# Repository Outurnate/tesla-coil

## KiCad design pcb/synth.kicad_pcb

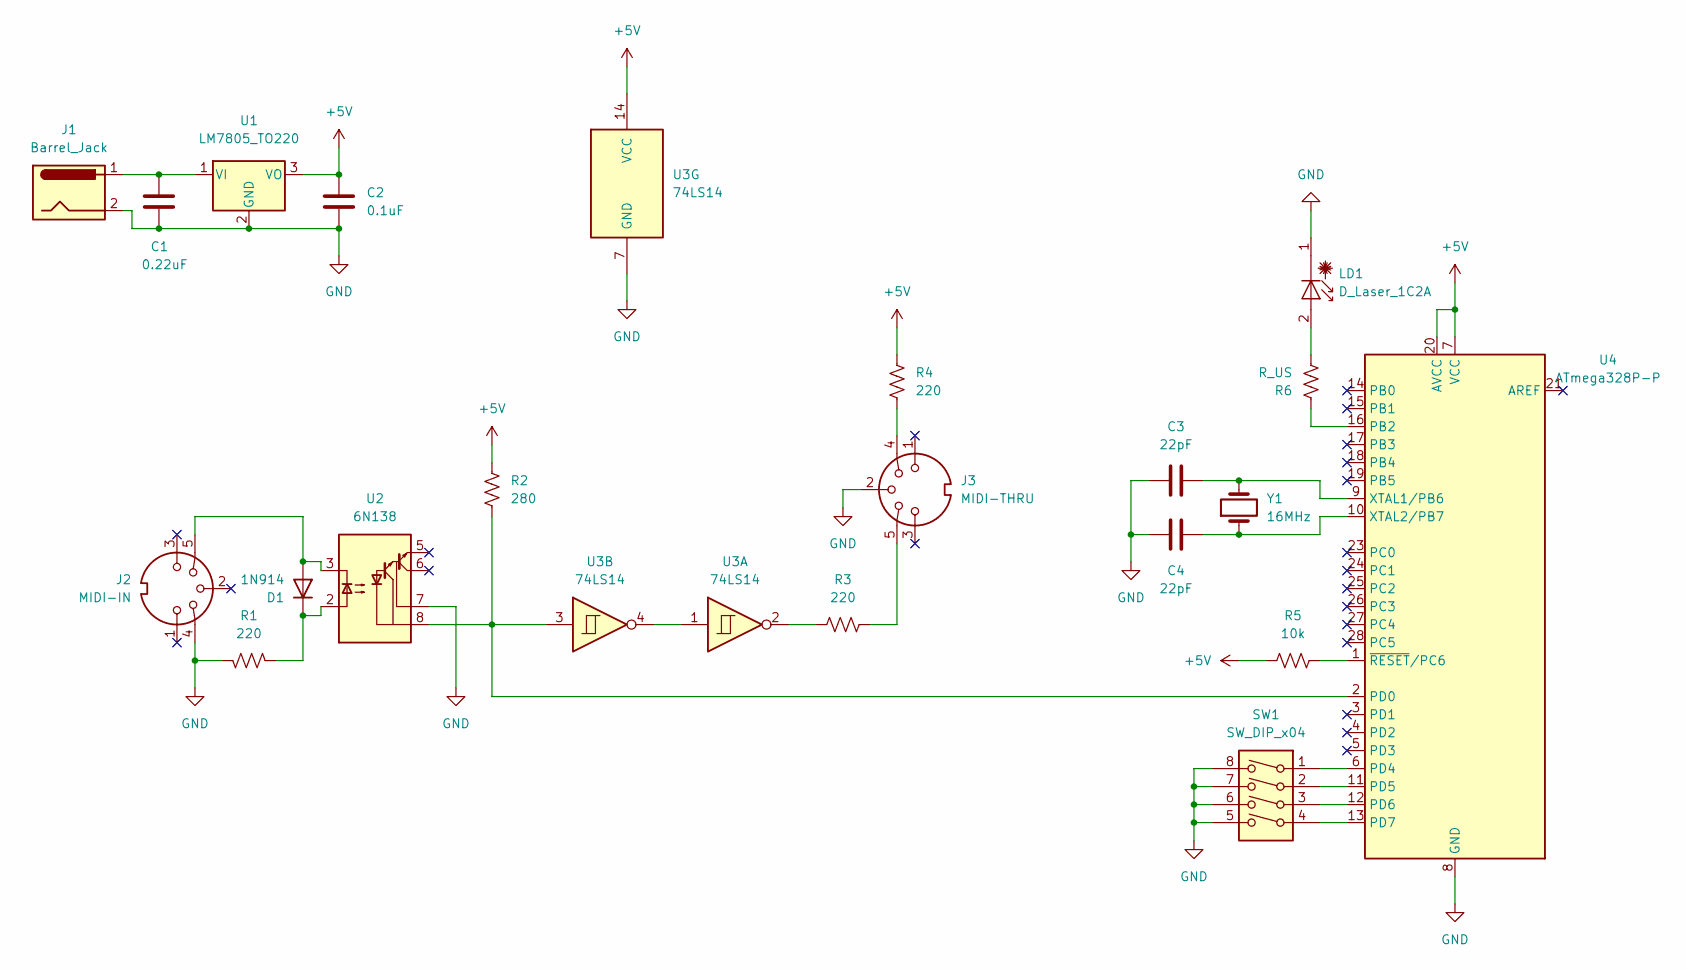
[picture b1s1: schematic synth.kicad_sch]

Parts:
C1: 0.22uF; C_Disc_D5.0mm_W2.5mm_P2.50mm
C2: 0.1uF; C_Disc_D5.0mm_W2.5mm_P2.50mm
C3, C4: 22pF; C_Disc_D5.0mm_W2.5mm_P2.50mm
D1: 1N914; D_DO-35_SOD27_P7.62mm_Horizontal
J1: Barrel_Jack; CUI_PJ-037A
J2: MIDI-IN; CUI_SDS-50J
J3: MIDI-THRU; CUI_SDS-50J
LD1: D_Laser_1C2A; PinHeader_1x02_P2.54mm_Vertical
R1, R3, R4: 220; R_Axial_DIN0207_L6.3mm_D2.5mm_P10.16mm_Horizontal
R2: 280; R_Axial_DIN0207_L6.3mm_D2.5mm_P10.16mm_Horizontal
R5: 10k; R_Axial_DIN0207_L6.3mm_D2.5mm_P10.16mm_Horizontal
R6: R_US; R_Axial_DIN0207_L6.3mm_D2.5mm_P10.16mm_Horizontal
SW1: SW_DIP_x04; SW_DIP_SPSTx04_Slide_9.78x12.34mm_W7.62mm_P2.54mm
U1: LM7805_TO220; TO-220-3_Vertical
U2: 6N138; DIP-8_W7.62mm_Socket
U3: 74LS14; DIP-14_W7.62mm_Socket
U4: ATmega328P-P; DIP-28_W7.62mm_Socket
Y1: 16MHz; Crystal_HC49-U_Vertical

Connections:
+5V: C2.1, R2.1, R4.1, R5.2, U1.3 (VO), U3.14 (VCC), U4.7 (VCC), U4.20 (AVCC)
GND: C1.2, C2.2, C3.2, C4.1, J1.2, J2.4, J3.2, LD1.1 (K), R1.2, SW1.5, SW1.6, SW1.7, SW1.8, U1.2 (GND), U2.7 (VO1), U3.7 (GND), U4.8 (GND), U4.22 (GND)
unnamed: C1.1, J1.1, U1.1 (VI)
unnamed: C3.1, U4.9 (XTAL1/PB6), Y1.2
unnamed: C4.2, U4.10 (XTAL2/PB7), Y1.1
unnamed: D1.1 (K), R1.1, U2.2 (C1)
unnamed: D1.2 (A), J2.5, U2.3 (C2)
unnamed: J3.4, R4.2
unnamed: J3.5, R3.1
unnamed: LD1.2 (A), R6.2
unnamed: R2.2, U2.8 (VCC), U3.3, U4.2 (PD0)
unnamed: R3.2, U3.2
unnamed: R5.1, U4.1 (~RESET/PC6)
unnamed: R6.1, U4.16 (PB2)
unnamed: SW1.1, U4.6 (PD4)
unnamed: SW1.2, U4.11 (PD5)
unnamed: SW1.3, U4.12 (PD6)
unnamed: SW1.4, U4.13 (PD7)
unnamed: U3.1, U3.4

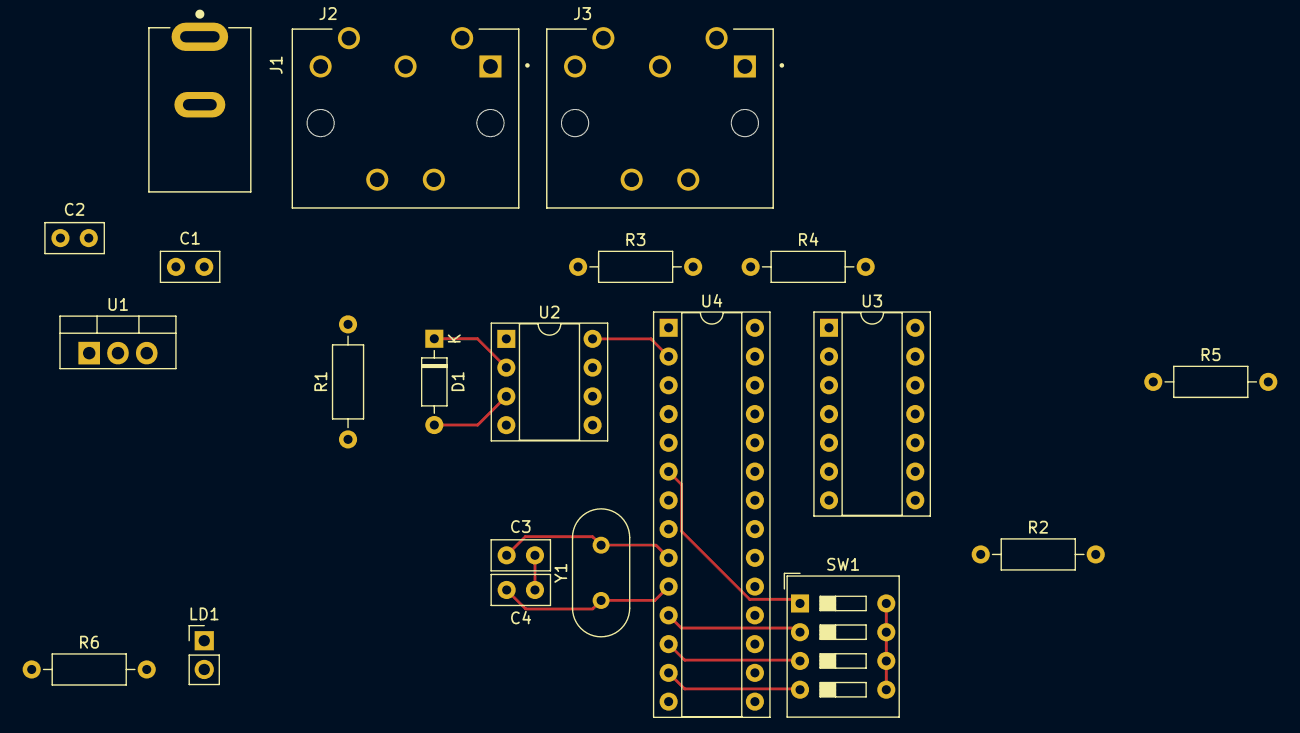
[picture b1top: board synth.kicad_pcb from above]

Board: 2 copper layers, 21 parts (0 on the bottom side), 19 nets.

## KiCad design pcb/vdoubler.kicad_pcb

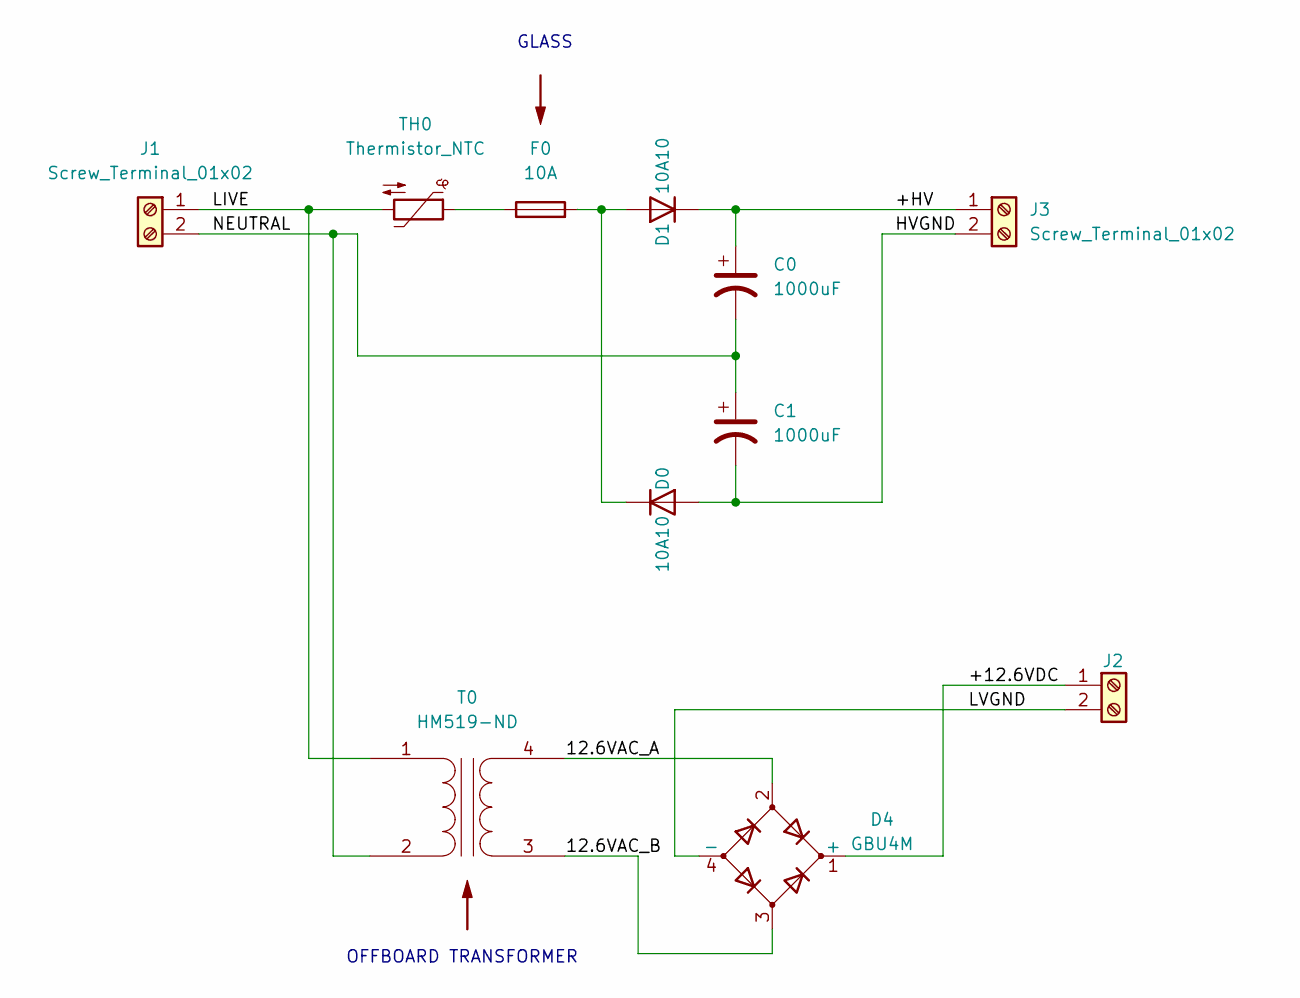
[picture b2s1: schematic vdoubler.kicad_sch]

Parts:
C0, C1: 1000uF; CP_Radial_D30.0mm_P10.00mm_SnapIn; DigiKey Part Number 399-ELH108M250AS5AA-ND
D0, D1: 10A10; D_P600_R-6_P12.70mm_Horizontal; DigiKey Part Number 3191-10A10-C1-3000-ND
D4: GBU4M; Diode_Bridge_Vishay_GBU; DigiKey Part Number GBU4M-ND
F0: 10A; Fuseholder_Cylinder-5x20mm_Bulgin_FX0456_Vertical_Closed; DigiKey Part Number 708-1427-ND
J1, J2, J3: Screw_Terminal_01x02; TE_1546833-2; DigiKey Part Number A112378-ND
T0: HM519-ND; TE_1546833-4; DigiKey Part Number HM519-ND
TH0: Thermistor_NTC; RV_Disc_D21.5mm_W4.3mm_P10mm; DigiKey Part Number 570-1354-ND

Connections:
/12.6VAC_A: D4.2, T0.4 (SB)
/12.6VAC_B: D4.3, T0.3 (SA)
/+12.6VDC: D4.1 (+), J2.1
/+HV: C0.1, D1.1 (K), J3.1
/HVGND: C1.2, D0.2 (A), J3.2
/LIVE: J1.1, T0.1 (AA), TH0.2
/LVGND: D4.4 (-), J2.2
/NEUTRAL: C0.2, C1.1, J1.2, T0.2 (AB)
unnamed: D0.1 (K), D1.2 (A), F0.2
unnamed: F0.1, TH0.1

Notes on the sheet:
GLASS
OFFBOARD TRANSFORMER

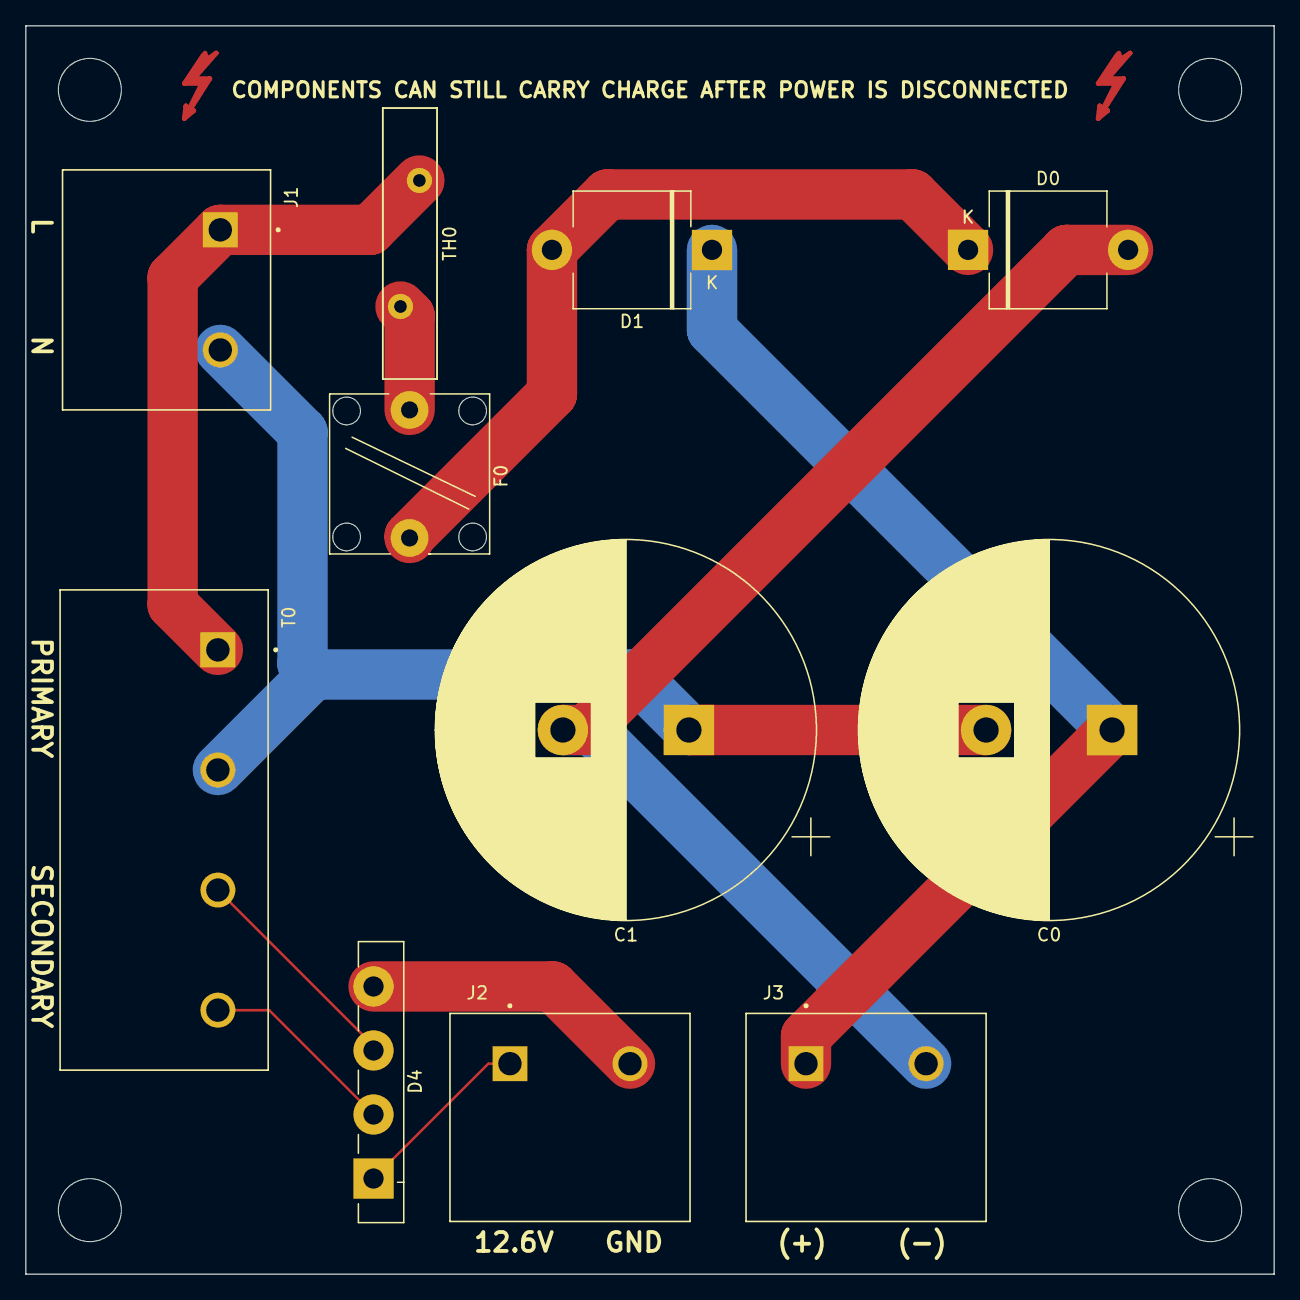
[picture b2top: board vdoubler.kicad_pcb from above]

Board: 2 copper layers, 99.1 x 99.1 mm, 11 parts (0 on the bottom side), 10 nets.

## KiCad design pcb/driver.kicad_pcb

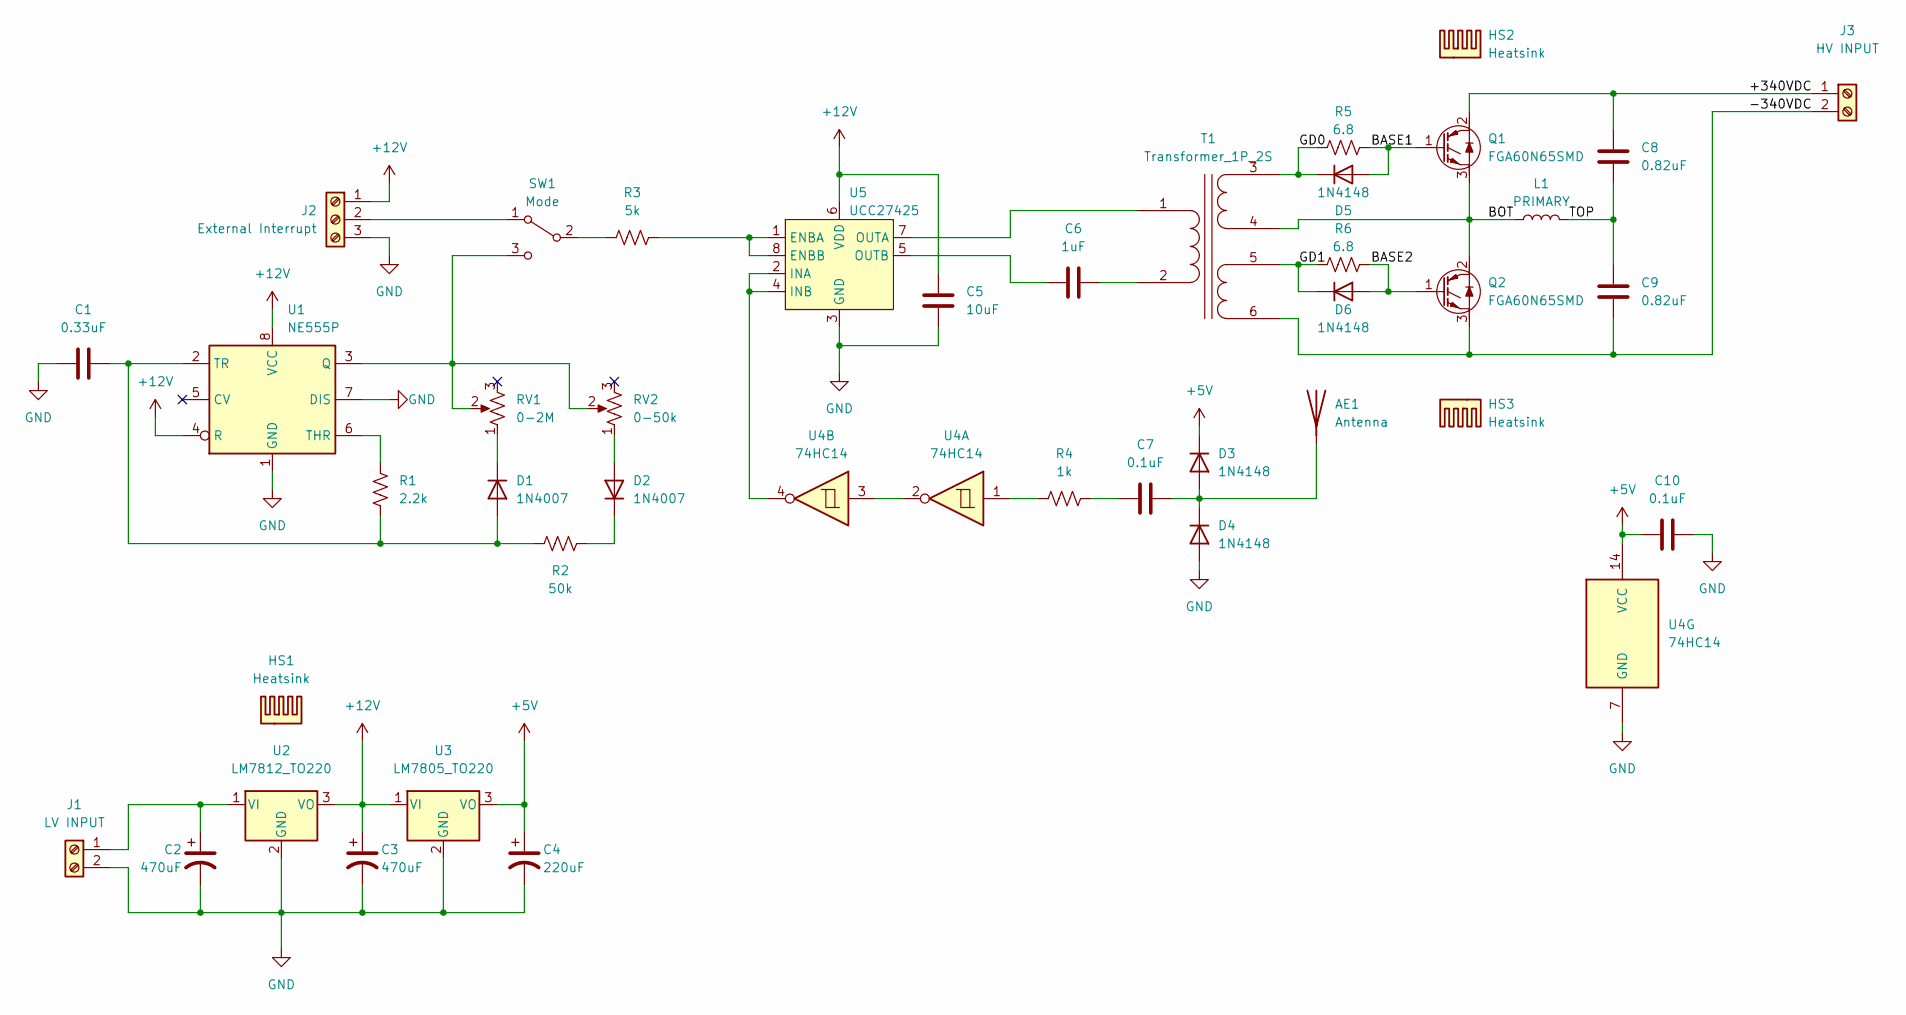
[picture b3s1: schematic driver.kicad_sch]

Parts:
AE1: Antenna; PinHeader_1x01_P2.54mm_Vertical
C1: 0.33uF; C_Rect_L7.0mm_W3.5mm_P5.00mm; DigiKey Part Number 445-180638-1-ND
C2, C3: 470uF; CP_Radial_D10.0mm_P5.00mm; DigiKey Part Number 1189-1869-ND
C4: 220uF; CP_Radial_D8.0mm_P3.50mm; DigiKey Part Number 732-8829-1-ND
C5: 10uF; C_Rect_L7.0mm_W3.5mm_P5.00mm; DigiKey Part Number 445-FG26X7R1E106KRT00-ND
C6: 1uF; C_Rect_L7.0mm_W3.5mm_P5.00mm; DigiKey Part Number 445-FG24X7R1H105KRT00-ND
C7, C10: 0.1uF; C_Rect_L11.0mm_W2.8mm_P10.00mm_MKT; DigiKey Part Number 1572-1638-ND
C8, C9: 0.82uF; C_Rect_L16.5mm_W4.9mm_P15.00mm_MKT; DigiKey Part Number P122566-ND
D1, D2: 1N4007; D_DO-41_SOD81_P10.16mm_Horizontal; DigiKey Part Number 1N4007GDICT-ND
D3, D4, D5, D6: 1N4148; D_DO-35_SOD27_P7.62mm_Horizontal; DigiKey Part Number 1N4148FS-ND
HS1: Heatsink; DigiKey Part Number A10755-ND
HS2, HS3: Heatsink; DigiKey Part Number 102-4229-ND
J1: LV INPUT; TE_1546833-2; DigiKey Part Number A112378-ND
J2: External Interrupt; 282834-3; DigiKey Part Number A98334-ND
J3: HV INPUT; TE_1546833-2; DigiKey Part Number A112379-ND
L1: PRIMARY; TE_1546833-2; DigiKey Part Number A112378-ND
Q1, Q2: FGA60N65SMD; TO-3P-3_Vertical_Heatsink; DigiKey Part Number FGA60N65SMDFS-ND
R1: 2.2k; R_Axial_DIN0207_L6.3mm_D2.5mm_P7.62mm_Horizontal; DigiKey Part Number CF14JT2K20TR-ND
R2: 50k; R_Axial_DIN0207_L6.3mm_D2.5mm_P10.16mm_Horizontal; DigiKey Part Number RN60C5002DB14-ND
R3: 5k; R_Axial_DIN0207_L6.3mm_D2.5mm_P7.62mm_Horizontal; DigiKey Part Number BC4514CT-ND
R4: 1k; R_Axial_DIN0207_L6.3mm_D2.5mm_P7.62mm_Horizontal
R5, R6: 6.8; R_Axial_DIN0207_L6.3mm_D2.5mm_P10.16mm_Horizontal; DigiKey Part Number 2019-MOSX1CT528R6R8JCT-ND
RV1: 0-2M; 282834-2; DigiKey Part Number A98333-ND
RV2: 0-50k; 282834-2; DigiKey Part Number A98333-ND
SW1: Mode; 282834-3; DigiKey Part Number A98334-ND
T1: Transformer_1P_2S; GDT; DigiKey Part Number 1934-1153-ND
U1: NE555P; DIP-8_W7.62mm; DigiKey Part Number 296-NE555P-ND
U2: LM7812_TO220; TO-220-3_Vertical; DigiKey Part Number MC7812ACTGOS-ND
U3: LM7805_TO220; TO-220-3_Vertical; DigiKey Part Number MC7805CTGOS-ND
U4: 74HC14; DIP-8_W7.62mm
U5: UCC27425; DIP-8_W7.62mm; DigiKey Part Number 296-1577-5-ND

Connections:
+5V: C4.1, C10.1, D3.1 (K), U3.3 (VO), U4.14 (VCC)
+12V: C3.1, C5.1, J2.1, U1.4 (R), U1.8 (VCC), U2.3 (VO), U3.1 (VI), U5.6 (VDD)
/+340VDC: C8.1, J3.1, Q1.2 (C)
/-340VDC: C9.2, J3.2, Q2.3 (E), T1.6 (SD)
/BASE1: D5.2 (A), Q1.1 (G), R5.1
/BASE2: D6.2 (A), Q2.1 (G), R6.1
/BOT: L1.1, Q1.3 (E), Q2.2 (C), T1.4 (SB)
/GD0: D5.1 (K), R5.2, T1.3 (SA)
/GD1: D6.1 (K), R6.2, T1.5 (SC)
/TOP: C8.2, C9.1, L1.2
GND: C1.2, C2.2, C3.2, C4.2, C5.2, C10.2, D4.2 (A), J1.2, J2.3, U1.1 (GND), U1.7 (DIS), U2.2 (GND), U3.2 (GND), U4.7 (GND), U5.3 (GND)
unnamed: AE1.1 (A), C7.2, D3.2 (A), D4.1 (K)
unnamed: C7.1, R4.1
unnamed: C1.1, D1.2 (A), R1.2, R2.2, U1.2 (TR)
unnamed: D1.1 (K), RV1.1
unnamed: D2.2 (A), RV2.1
unnamed: D2.1 (K), R2.1
unnamed: C2.1, J1.1, U2.1 (VI)
unnamed: J2.2, SW1.1 (A)
unnamed: R4.2, U4.1
unnamed: R3.2, SW1.2 (B)
unnamed: RV1.2, RV2.2, SW1.3 (C), U1.3 (Q)
unnamed: T1.1 (AA), U5.7 (OUTA)
unnamed: C6.1, T1.2 (AB)
unnamed: R1.1, U1.6 (THR)
unnamed: U4.2, U4.3
unnamed: R3.1, U5.1 (ENBA), U5.8 (ENBB)
unnamed: U4.4, U5.2 (INA), U5.4 (INB)
unnamed: C6.2, U5.5 (OUTB)

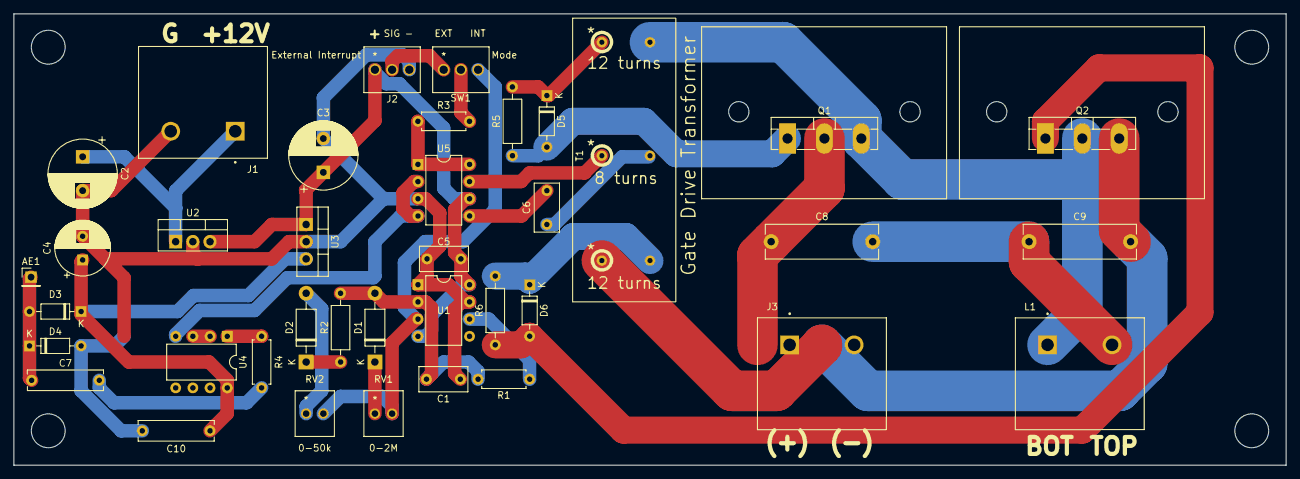
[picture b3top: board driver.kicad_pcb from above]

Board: 2 copper layers, 188.0 x 66.7 mm, 38 parts (0 on the bottom side), 29 nets.

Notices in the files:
parts and their libraries:
Copyright 2021 Accelerated Designs. All rights reserved.
